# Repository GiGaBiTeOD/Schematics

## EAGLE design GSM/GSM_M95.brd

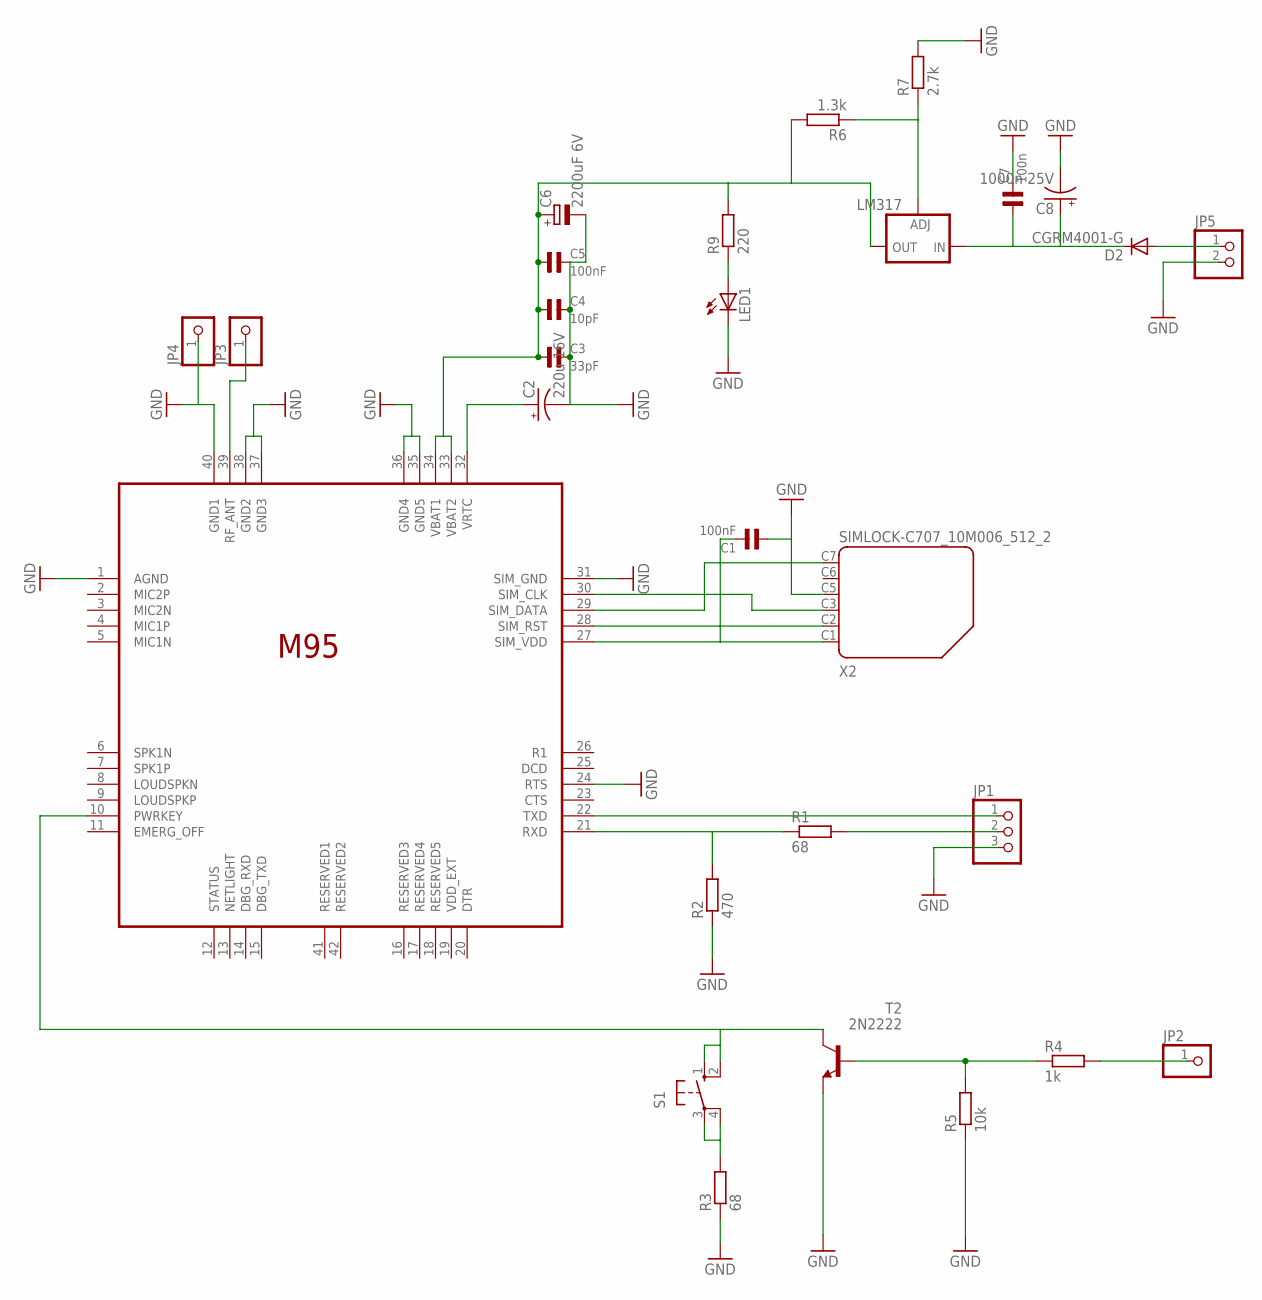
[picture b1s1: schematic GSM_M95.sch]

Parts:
C1, C5: 100nF; 1206
C2: 220u 16V; UD-6,3X7,7_NICHICON
C3: 33pF; 1206
C4: 10pF; 1206
C6: 2200uF 6V; E5-10,5
C7: 100n; 1206
C8: 1000n 25V; E5-13
D2: CGRM4001-G; SOD-123_MINI-SMA
JP1: PINHD-1X3; 1X03
JP2, JP3, JP4: PINHD-1X1; 1X01
JP5: PINHD-1X2; 1X02
LED1: LED3MM
LM317: LM317TL; 317TL
M95: M95_HD_V1.0; M95
R1, R3: 68; R1206W
R2: 470; R1206W
R4: 1k; R1206W
R5: 10k; R1206W
R6: 1.3k; R1206W
R7: 2.7k; R1206W
R9: 220; R0805
S1: 10-XX; B3F-10XX
T2: 2N2222; TO92-EBC
X2: SIMLOCK-C707_10M006_512_2; C707_10M006_512_2

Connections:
GND: C1.1, C2.-, C3.2, C4.2, C5.2, C6.-, C7.2, C8.-, JP1.3, JP4.1, JP5.2, LED1.K (C), M95.1 (AGND), M95.24 (RTS), M95.31 (SIM_GND), M95.35 (GND5), M95.36 (GND4), M95.37 (GND3), M95.38 (GND2), M95.40 (GND1), R2.1, R3.1, R5.1, R7.2, T2.E, X2.C5 (4)
unnamed: M95.21 (RXD), R1.1, R2.2
unnamed: JP1.2, R1.2
unnamed: LM317.1 (ADJ), R6.1, R7.1
unnamed: M95.10 (PWRKEY), S1.1 (S), S1.2 (S1), T2.C
unnamed: JP1.1, M95.22 (TXD)
unnamed: R3.2, S1.3, S1.4 (P1)
unnamed: C2.+, M95.32 (VRTC)
unnamed: C3.1, C4.1, C5.1, C6.+, LM317.2 (OUT), M95.33 (VBAT2), M95.34 (VBAT1), R6.2, R9.2
unnamed: R4.1, R5.2, T2.B
unnamed: C1.2, M95.27 (SIM_VDD), X2.C1 (1)
unnamed: JP3.1, M95.39 (RF_ANT)
unnamed: C7.1, C8.+, D2.C, LM317.3 (IN)
unnamed: JP2.1, R4.2
unnamed: M95.28 (SIM_RST), X2.C2 (2)
unnamed: M95.29 (SIM_DATA), X2.C7 (6)
unnamed: M95.30 (SIM_CLK), X2.C3 (3)
unnamed: LED1.A, R9.1
unnamed: D2.A, JP5.1

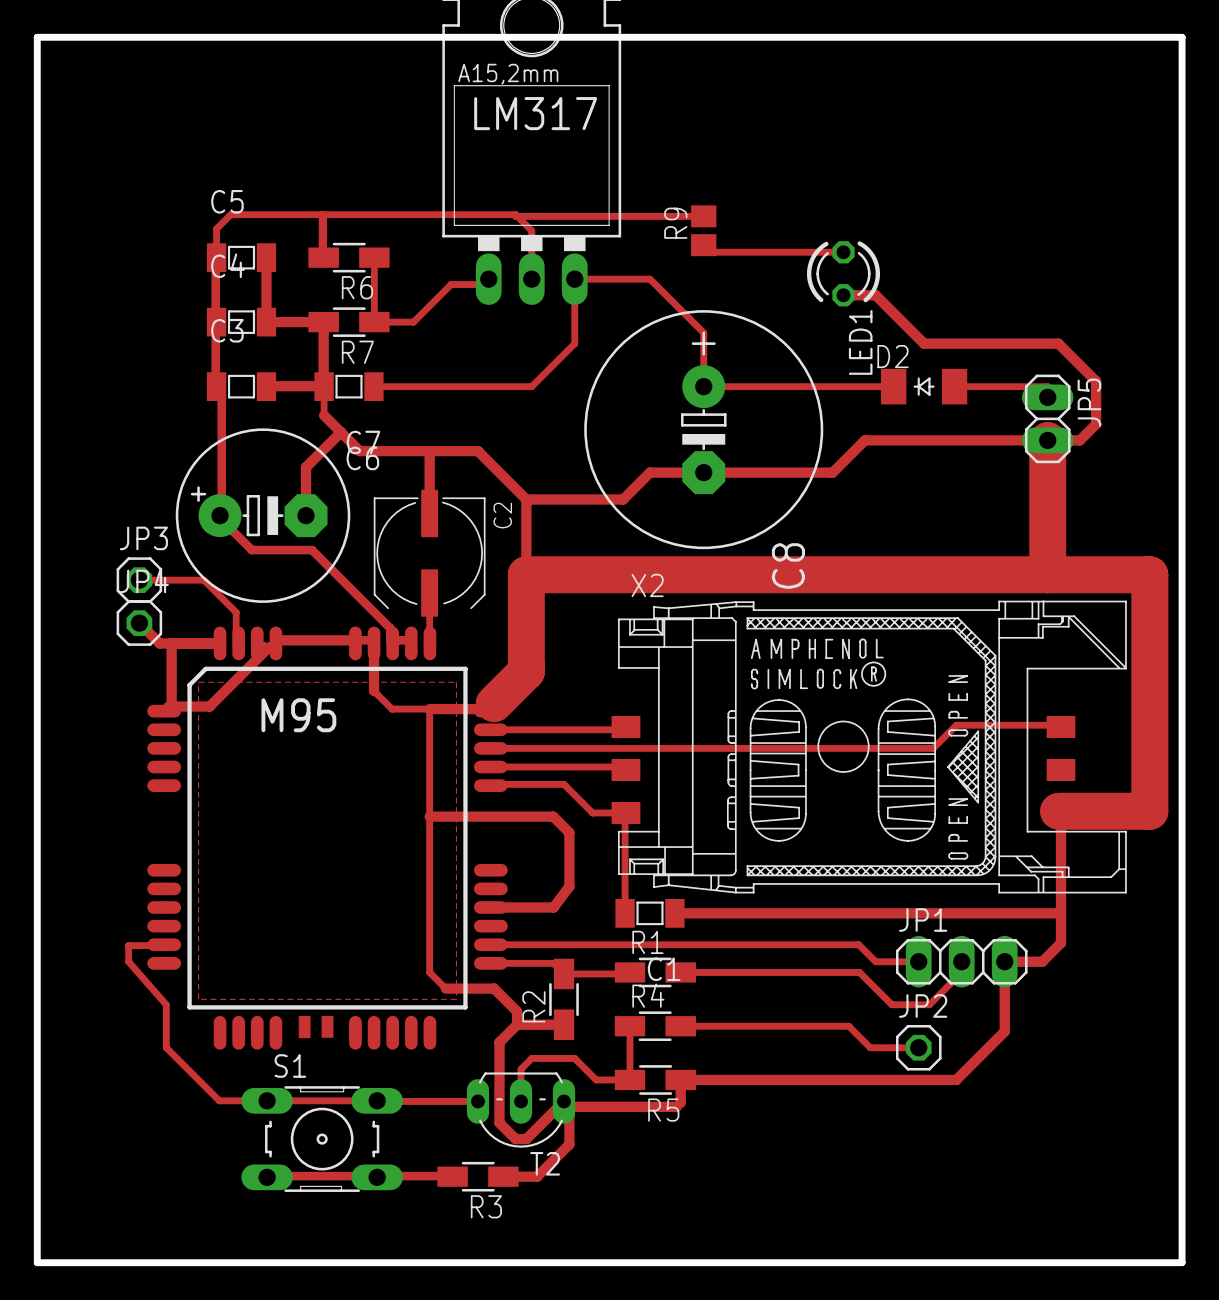
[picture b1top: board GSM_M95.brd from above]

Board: 2 copper layers, 67.6 x 72.4 mm, 28 parts (0 on the bottom side), 19 nets.

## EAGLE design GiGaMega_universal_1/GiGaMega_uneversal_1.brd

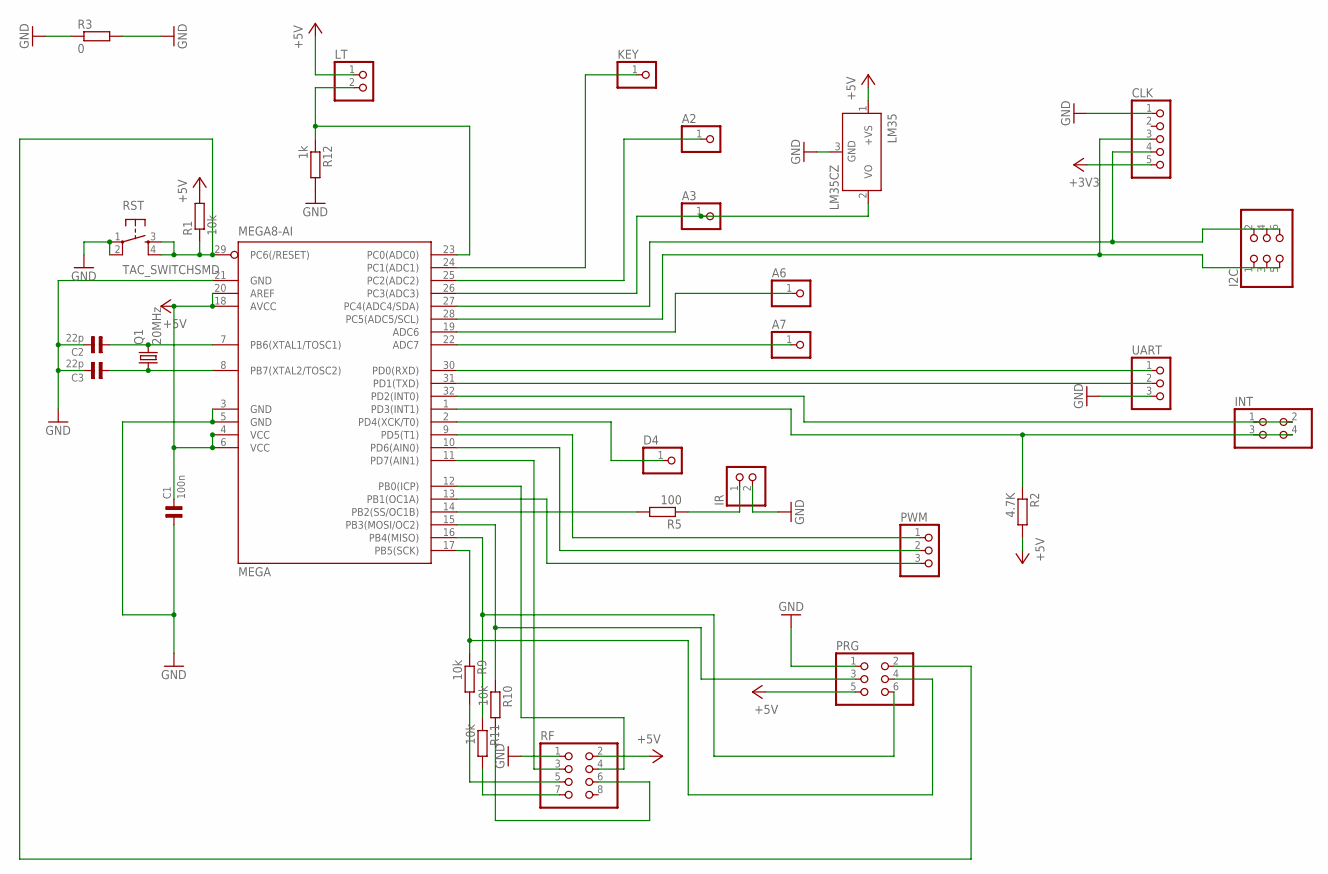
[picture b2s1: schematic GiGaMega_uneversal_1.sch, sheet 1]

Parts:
A2, A3, A6, A7: PINHD-1X1; 1X01
C1: 100n; 1206
C2, C3: 22p; 1206
CLK: PINHD-1X5; 1X05
D4: PINHD-1X1; 1X01
I2C: PINHD-2X3; 2X03
INT: PINHD-2X2; 2X02
IR: PINHD-1X2; 1X02
KEY: PINHD-1X1; 1X01
LM35: LM35CZ; TO92
LT: PINHD-1X2; 1X02
MEGA: MEGA8-AI; TQFP32-08
PRG: PINHD-2X3; 2X03
PWM: PINHD-1X3; 1X03
Q1: 20MHz; HC49UP
R1, R9, R10, R11: 10k; R1206
R2: 4.7K; R1206
R3: 0; R1206
R5: 100; R1206
R12: 1k; R1206
RF: PINHD-2X4; 2X04
RST: TAC_SWITCHSMD; TACTILE-SWITCH-SMD
UART: PINHD-1X3; 1X03

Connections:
+3V3: CLK.5; also elsewhere on the board
+5V: C1.2, LM35.1 (+VS), LT.1, MEGA.4 (VCC), MEGA.6 (VCC), MEGA.18 (AVCC), MEGA.20 (AREF), PRG.5, R1.2, R2.2, RF.2; also elsewhere on the board
GND: C1.1, C2.2, C3.2, CLK.1, IR.2, LM35.3 (GND), MEGA.3 (GND), MEGA.5 (GND), MEGA.21 (GND), PRG.1, R3.1, R3.2, R12.2, RF.1, RST.1, RST.2, UART.3; also elsewhere on the board
KEY_PIN24: KEY.1, MEGA.24 (PC1(ADC1))
MISO: MEGA.16 (PB4(MISO)), PRG.6, R11.1
MOSI: MEGA.15 (PB3(MOSI/OC2)), PRG.3, R10.1
unnamed: A2.1, MEGA.25 (PC2(ADC2))
unnamed: D4.1, MEGA.2 (PD4(XCK/T0))
unnamed: INT.3, INT.4, MEGA.1 (PD3(INT1)), R2.1
unnamed: R10.2, RF.6
unnamed: R11.2, RF.7
unnamed: R9.2, RF.5
PIN1_IRLED: IR.1, R5.1
PIN2: MEGA.9 (PD5(T1)), PWM.1
PIN7: C2.1, MEGA.7 (PB6(XTAL1/TOSC1)), Q1.2
PIN8: C3.1, MEGA.8 (PB7(XTAL2/TOSC2)), Q1.1
PIN9: MEGA.10 (PD6(AIN0)), PWM.2
PIN10: MEGA.13 (PB1(OC1A)), PWM.3
PIN11: MEGA.11 (PD7(AIN1)), RF.3
PIN12: MEGA.12 (PB0(ICP)), RF.4
PIN14: MEGA.14 (PB2(SS/OC1B)), R5.2
PIN19: A6.1, MEGA.19 (ADC6)
PIN22: A7.1, MEGA.22 (ADC7)
PIN23: LT.2, MEGA.23 (PC0(ADC0)), R12.1
PIR_: A3.1, LM35.2 (VO), MEGA.26 (PC3(ADC3))
PIR_WATER: INT.1, INT.2, MEGA.32 (PD2(INT0))
RESET: MEGA.29 (PC6(/RESET)), PRG.2, R1.1, RST.3, RST.4
RX: MEGA.30 (PD0(RXD)), UART.1
SCK: MEGA.17 (PB5(SCK)), PRG.4, R9.1
SCL: CLK.3, I2C.1, I2C.3, I2C.5, MEGA.28 (PC5(ADC5/SCL))
SDA: CLK.4, I2C.2, I2C.4, I2C.6, MEGA.27 (PC4(ADC4/SDA))
TX: MEGA.31 (PD1(TXD)), UART.2

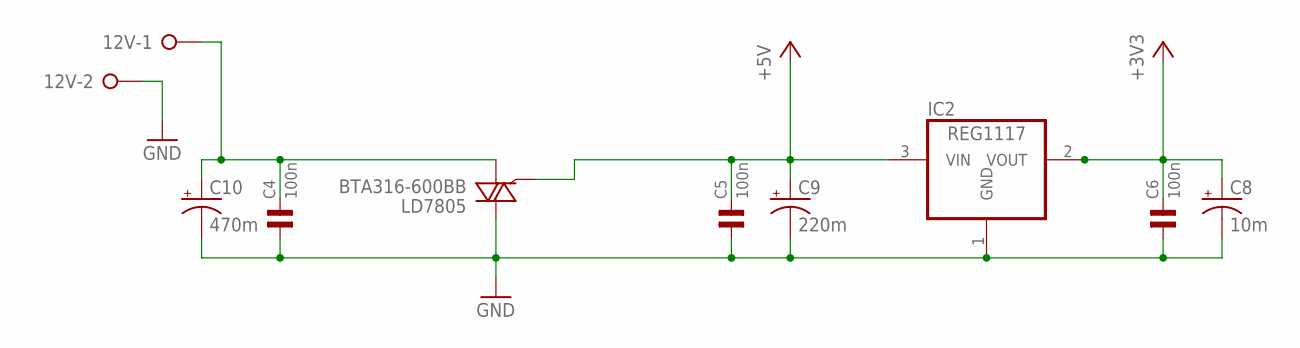
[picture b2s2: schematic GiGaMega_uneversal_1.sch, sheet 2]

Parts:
12V: W237-02P; W237-132
C4, C5, C6: 100n; 1206
C8: 10m; UD-4X5,8_NICHICON
C9: 220m; UD-6,3X7,7_NICHICON
C10: 470m; UD-10X10_NICHICON
IC2: REG1117; SOT223
LD7805: BTA316-600BB; SOT404

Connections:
+3V3: C6.2, C8.+, IC2.2 (VOUT); also elsewhere on the board
+5V: C5.2, C9.+, IC2.3 (VIN), LD7805.3 (G); also elsewhere on the board
+12: 12V.1, C4.2, C10.+, LD7805.1 (CM)
GND: 12V.2, C4.1, C5.1, C6.1, C8.-, C9.-, C10.-, IC2.1 (GND), LD7805.MB (LD); also elsewhere on the board

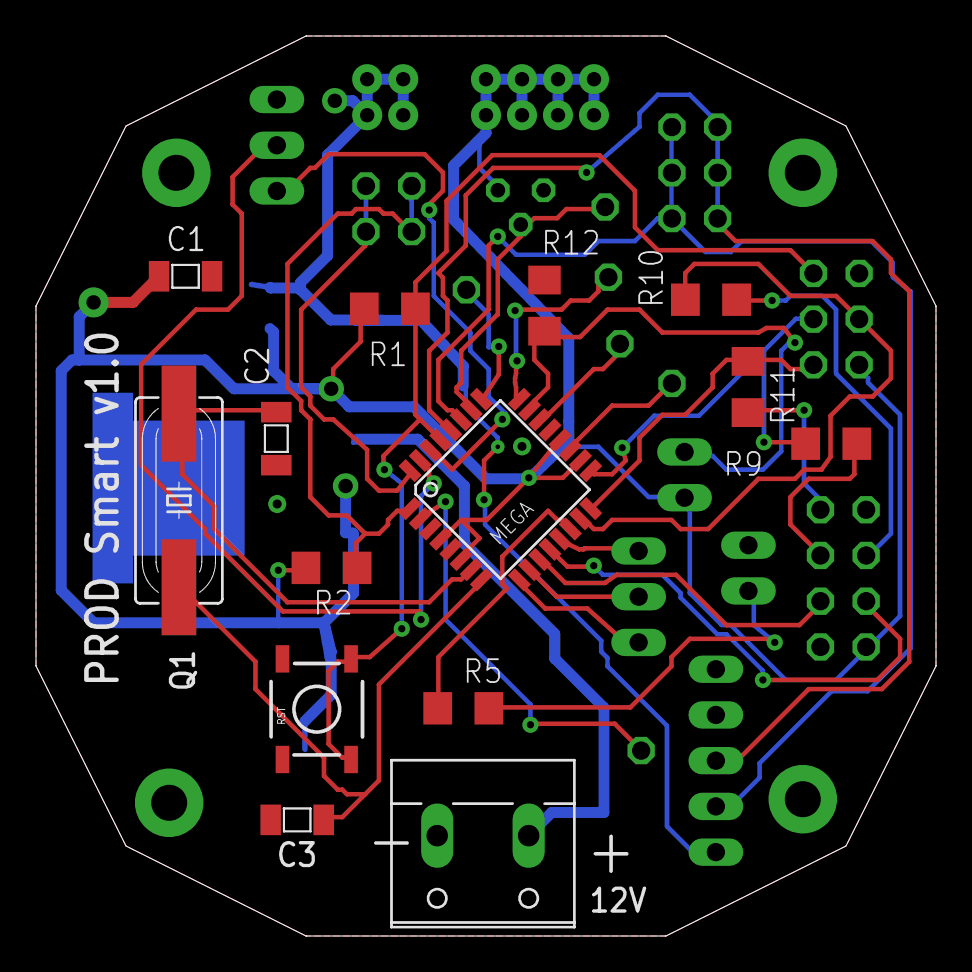
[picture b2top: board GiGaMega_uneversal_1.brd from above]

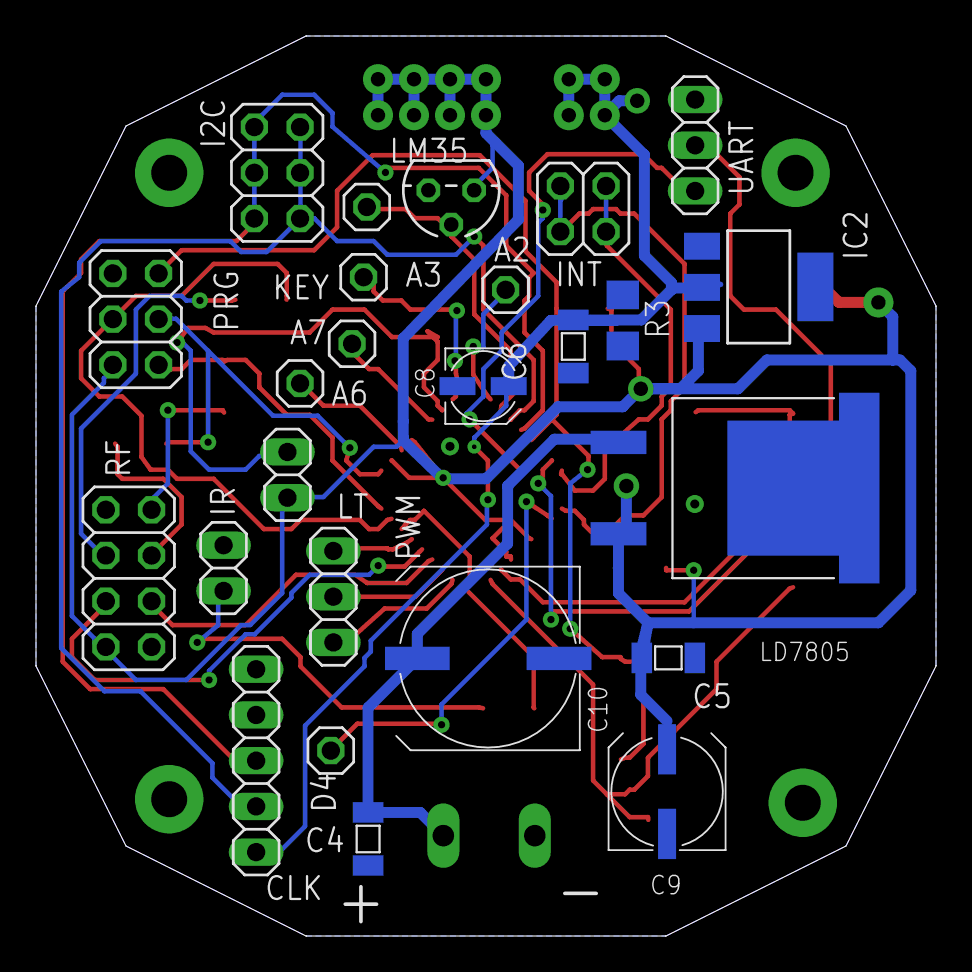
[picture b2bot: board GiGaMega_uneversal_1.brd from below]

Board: 2 copper layers, 50.0 x 50.0 mm, 39 parts (25 on the bottom side), 33 nets.

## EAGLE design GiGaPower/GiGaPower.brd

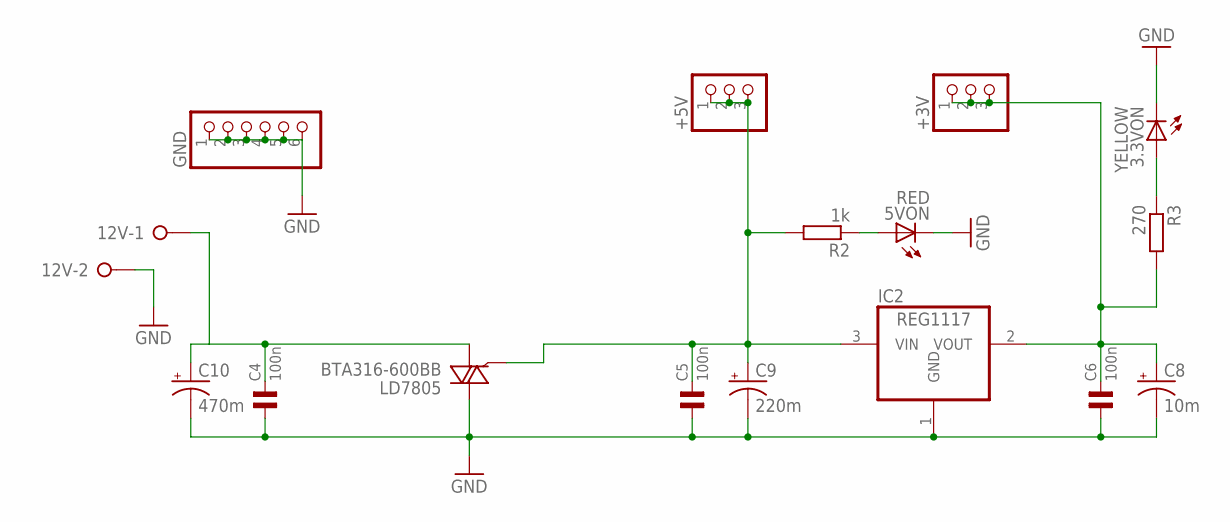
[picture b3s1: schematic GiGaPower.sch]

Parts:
3.3VON: YELLOW; CHIPLED_1206
5VON: RED; CHIPLED_1206
12V: W237-02P; W237-132
+3V, +5V: PINHD-1X3; 1X03
C4, C5, C6: 100n; 1206
C8: 10m; UD-4X5,8_NICHICON
C9: 220m; UD-6,3X7,7_NICHICON
C10: 470m; UD-10X10_NICHICON
GND: PINHD-1X6; 1X06
IC2: REG1117; SOT223
LD7805: BTA316-600BB; SOT404
R2: 1k; R1206
R3: 270; R1206

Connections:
GND: 3.3VON.C, 5VON.C, 12V.2, C4.1, C5.1, C6.1, C8.-, C9.-, C10.-, GND.1, GND.2, GND.3, GND.4, GND.5, GND.6, IC2.1 (GND), LD7805.MB (LD)
unnamed: 12V.1, C4.2, C10.+, LD7805.1 (CM)
unnamed: +5V.1, +5V.2, +5V.3, C5.2, C9.+, IC2.3 (VIN), LD7805.3 (G), R2.2
unnamed: +3V.1, +3V.2, +3V.3, C6.2, C8.+, IC2.2 (VOUT), R3.2
unnamed: 5VON.A, R2.1
unnamed: 3.3VON.A, R3.1

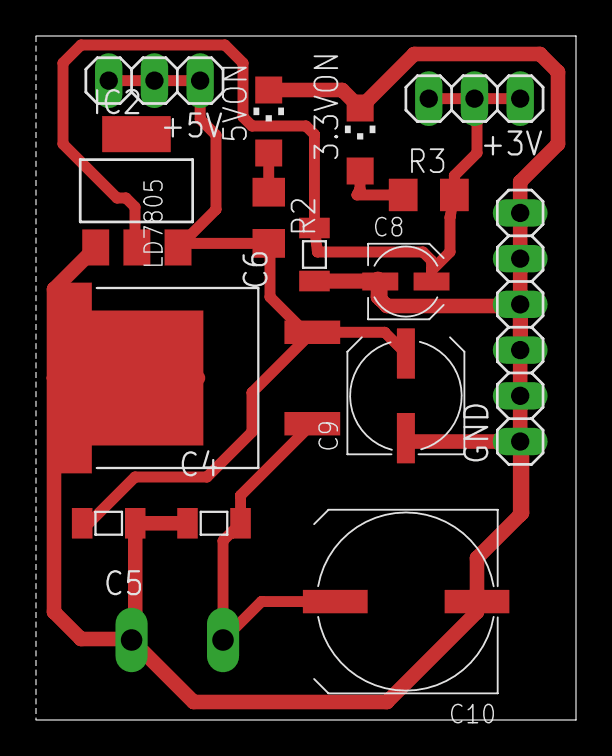
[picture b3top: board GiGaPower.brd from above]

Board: 2 copper layers, 30.0 x 38.0 mm, 16 parts (1 on the bottom side), 6 nets.

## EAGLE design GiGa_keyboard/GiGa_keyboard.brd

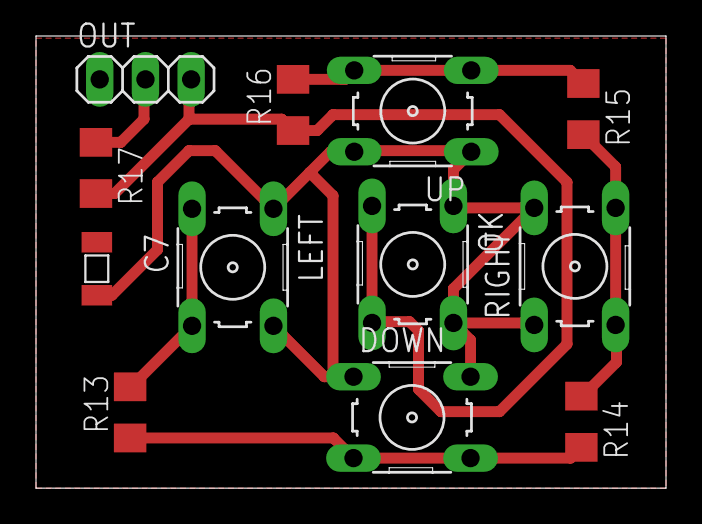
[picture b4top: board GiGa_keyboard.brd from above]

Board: 2 copper layers, 35.0 x 25.1 mm, 12 parts (0 on the bottom side), 8 nets.

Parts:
C7: 100nF; 1206
DOWN: B3F-10XX
LEFT: B3F-10XX
OK: B3F-10XX
OUT: 1X03
R13: 3k3; R1206
R14: 1k; R1206
R15: 620; R1206
R16: 330; R1206
R17: 10k; R1206
RIGHT: B3F-10XX
UP: B3F-10XX

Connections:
+5V: OUT.2, R17.1
ANALOG: OK.3, OK.4, OUT.3, R16.1, R17.2
GND: C7.1, OUT.1
unnamed: C7.2, DOWN.1, DOWN.2, LEFT.1, LEFT.2, OK.1, OK.2, RIGHT.1, RIGHT.2, UP.1, UP.2
unnamed: LEFT.3, LEFT.4, R13.2
unnamed: DOWN.3, DOWN.4, R13.1, R14.2
unnamed: R14.1, R15.2, RIGHT.3, RIGHT.4
unnamed: R15.1, R16.2, UP.3, UP.4

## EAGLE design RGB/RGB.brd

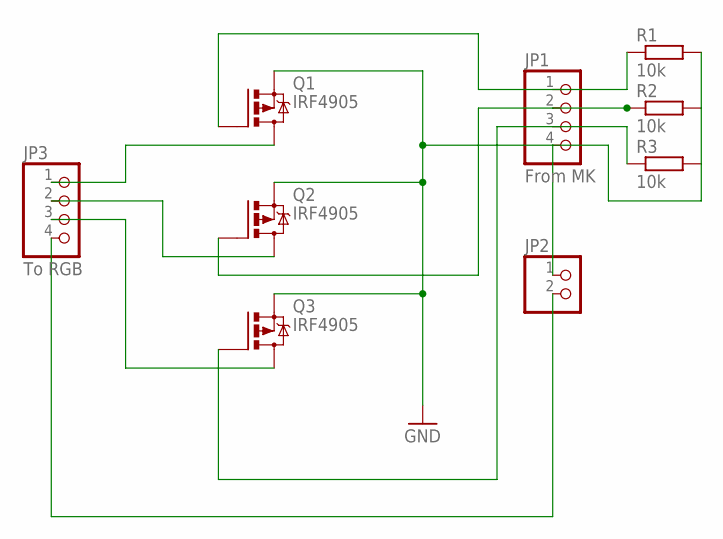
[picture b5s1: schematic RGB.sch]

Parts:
JP1: From MK; 1X04/90
JP2: PINHD-1X2/90; 1X02/90
JP3: To RGB; 1X04/90
Q1, Q2, Q3: IRF4905; TO220BH
R1, R2, R3: 10k; 0207/10

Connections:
GND: JP1.4, JP2.1, Q1.S, Q2.S, Q3.S, R1.2, R2.2, R3.2
unnamed: JP3.2, Q2.D
unnamed: JP3.3, Q3.D
unnamed: JP3.1, Q1.D
unnamed: JP2.2, JP3.4
unnamed: JP1.1, Q1.G, R1.1
unnamed: JP1.2, Q2.G, R2.1
unnamed: JP1.3, Q3.G, R3.1

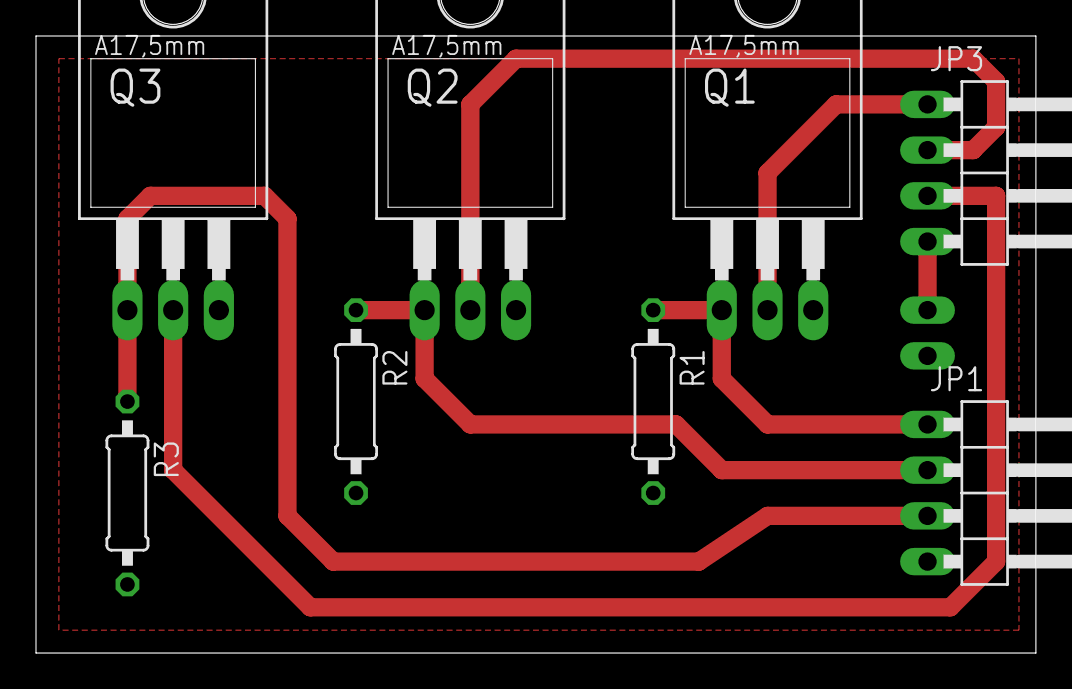
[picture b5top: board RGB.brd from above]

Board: 2 copper layers, 55.5 x 34.3 mm, 9 parts (1 on the bottom side), 8 nets.

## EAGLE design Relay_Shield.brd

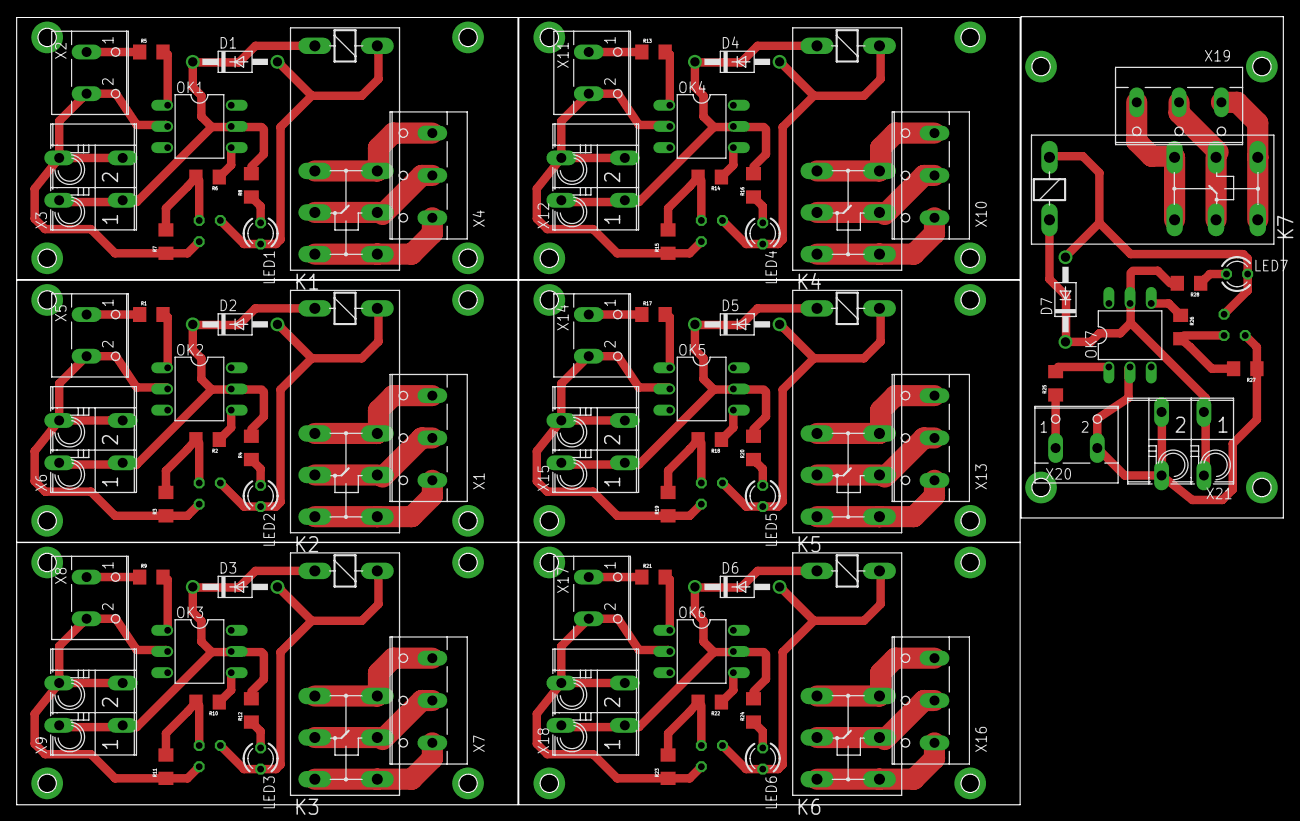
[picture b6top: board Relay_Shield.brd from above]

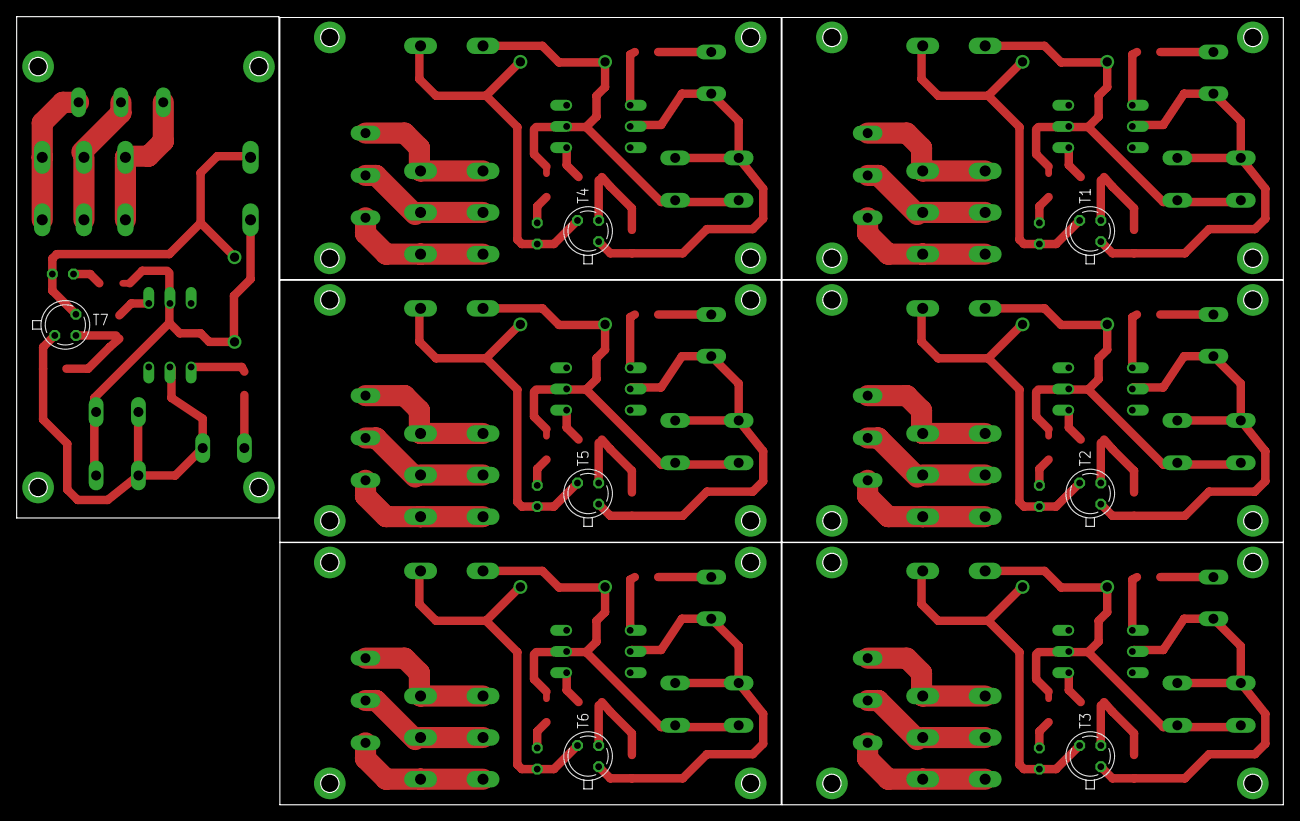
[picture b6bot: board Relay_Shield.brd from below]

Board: 2 copper layers, 152.0 x 94.6 mm, 84 parts (7 on the bottom side), 77 nets.

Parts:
D1, D2, D3, D4, D5, D6, D7: 1N4004; DO41-10
K1, K2, K3, K4, K5, K6, K7: G2RE
LED1, LED2, LED3, LED4, LED5, LED6, LED7: LED3MM
OK1, OK2, OK3, OK4, OK5, OK6, OK7: 4N25M; DIL06
R1, R2, R5, R6, R9, R10, R13, R14, R17, R18, R21, R22, R25, R26: 1K; 1206
R3, R7, R11, R15, R19, R23, R27: 10k; 1206
R4, R8, R12, R16, R20, R24, R28: 1.1K; 1206
T1, T2, T3, T4, T5, T6, T7: 2N2222; TO18
X1, X4, X7, X10, X13, X16, X19: W237-3E
X2, X5, X8, X11, X14, X17, X20: W237-102
X3, X6, X9, X12, X15, X18, X21: FFKV2

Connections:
+24V: D1.C, K1.1, OK1.5, R8.2, X3.1A
+24V1: D2.C, K2.1, OK2.5, R4.2, X6.1A
+24V2: D3.C, K3.1, OK3.5, R12.2, X9.1A
+24V3: D4.C, K4.1, OK4.5, R16.2, X12.1A
+24V4: D5.C, K5.1, OK5.5, R20.2, X15.1A
+24V5: D6.C, K6.1, OK6.5, R24.2, X18.1A
+24V6: D7.C, K7.1, OK7.5, R28.2, X21.1A
GND: OK1.2, R7.1, T1.1, X2.2, X3.2A
GND1: OK2.2, R3.1, T2.1, X5.2, X6.2A
GND2: OK3.2, R11.1, T3.1, X8.2, X9.2A
GND3: OK4.2, R15.1, T4.1, X11.2, X12.2A
GND4: OK5.2, R19.1, T5.1, X14.2, X15.2A
GND5: OK6.2, R23.1, T6.1, X17.2, X18.2A
GND6: OK7.2, R27.1, T7.1, X20.2, X21.2A
unnamed: OK1.1, R5.2
unnamed: OK1.4, R6.1
unnamed: R6.2, R7.2, T1.2
unnamed: R5.1, X2.1
unnamed: D1.A, K1.2, LED1.K, T1.3
unnamed: LED1.A, R8.1
unnamed: OK2.1, R1.2
unnamed: K1.P0, K1.P1, X4.2
unnamed: K1.O0, K1.O1, X4.3
unnamed: K1.S0, K1.S1, X4.1
unnamed: OK2.4, R2.1
unnamed: R2.2, R3.2, T2.2
unnamed: D2.A, K2.2, LED2.K, T2.3
unnamed: LED2.A, R4.1
unnamed: K2.P0, K2.P1, X1.2
unnamed: K2.O0, K2.O1, X1.3
unnamed: K2.S0, K2.S1, X1.1
unnamed: R1.1, X5.1
unnamed: OK3.1, R9.2
unnamed: OK3.4, R10.1
unnamed: R10.2, R11.2, T3.2
unnamed: D3.A, K3.2, LED3.K, T3.3
unnamed: LED3.A, R12.1
unnamed: K3.P0, K3.P1, X7.2
unnamed: K3.O0, K3.O1, X7.3
unnamed: K3.S0, K3.S1, X7.1
unnamed: R9.1, X8.1
unnamed: OK4.1, R13.2
unnamed: OK4.4, R14.1
unnamed: R14.2, R15.2, T4.2
unnamed: D4.A, K4.2, LED4.K, T4.3
unnamed: LED4.A, R16.1
unnamed: K4.P0, K4.P1, X10.2
unnamed: K4.O0, K4.O1, X10.3
unnamed: K4.S0, K4.S1, X10.1
unnamed: R13.1, X11.1
unnamed: OK5.1, R17.2
unnamed: OK5.4, R18.1
unnamed: R18.2, R19.2, T5.2
unnamed: D5.A, K5.2, LED5.K, T5.3
unnamed: LED5.A, R20.1
unnamed: K5.P0, K5.P1, X13.2
unnamed: K5.O0, K5.O1, X13.3
unnamed: K5.S0, K5.S1, X13.1
unnamed: R17.1, X14.1
unnamed: OK6.1, R21.2
unnamed: OK6.4, R22.1
unnamed: R22.2, R23.2, T6.2
unnamed: D6.A, K6.2, LED6.K, T6.3
unnamed: LED6.A, R24.1
unnamed: K6.P0, K6.P1, X16.2
unnamed: K6.O0, K6.O1, X16.3
unnamed: K6.S0, K6.S1, X16.1
unnamed: R21.1, X17.1
unnamed: OK7.1, R25.2
unnamed: OK7.4, R26.1
unnamed: R26.2, R27.2, T7.2
unnamed: D7.A, K7.2, LED7.K, T7.3
unnamed: LED7.A, R28.1
unnamed: K7.P0, K7.P1, X19.2
unnamed: K7.O0, K7.O1, X19.3
unnamed: K7.S0, K7.S1, X19.1
unnamed: R25.1, X20.1

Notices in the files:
parts and their libraries:
SparkFun-Retired: Licensing:Creative Commons ShareAlike 4.0 International - https://creativecommons.org/licenses/by-sa/4.0
